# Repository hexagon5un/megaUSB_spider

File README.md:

megaUSB_spider
==============

A programming spider to make developing V-USB devices easy.

See http://littlehacks.org/propack/vusb_prototyper for more info.

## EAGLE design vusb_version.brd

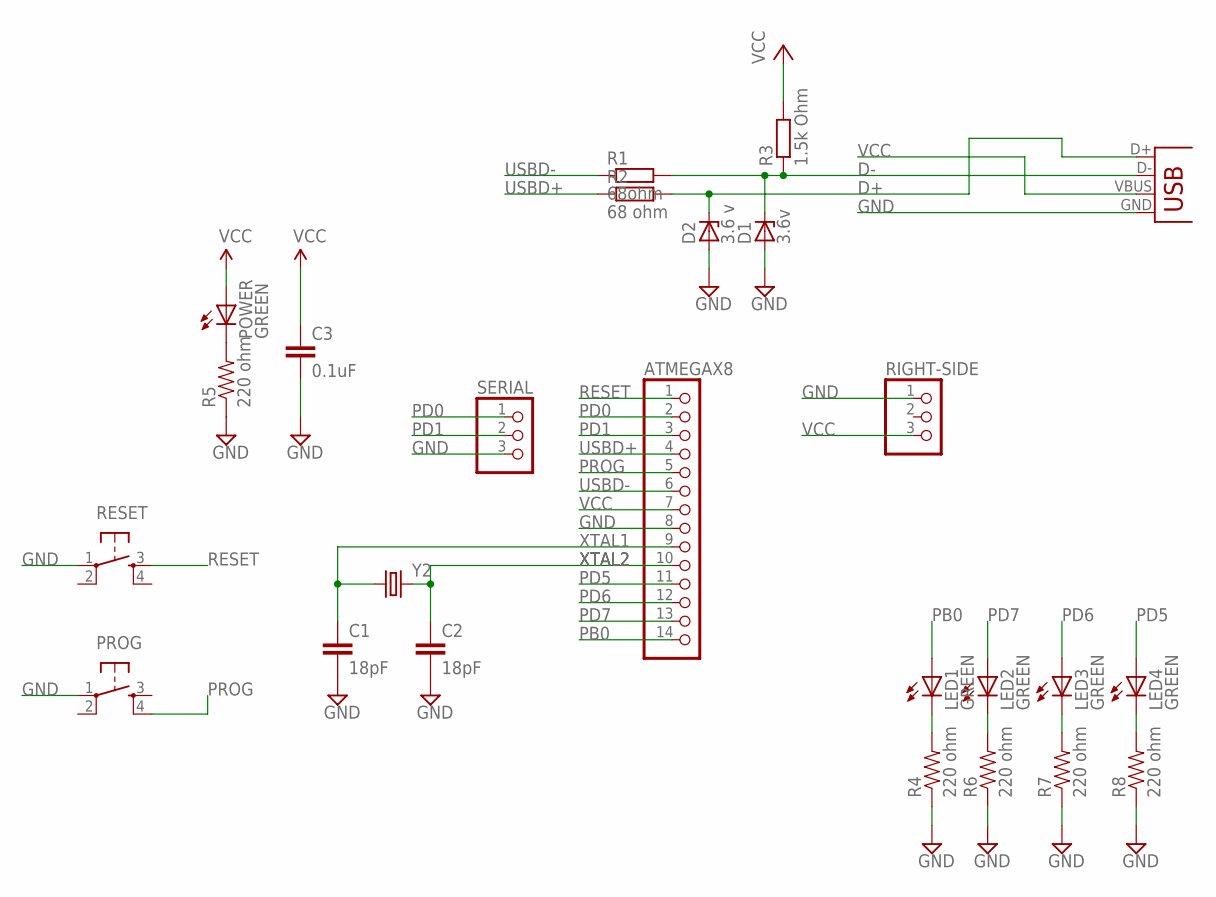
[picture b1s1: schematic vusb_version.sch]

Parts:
ATMEGAX8: PINHD-1X14; 1X14
C1, C2: 18pF; 1206
C3: 0.1uF; 1206
D1: 3.6v; SOT23
D2: 3.6 v; SOT23
JP1: USBSMD; USB-MINIB
LED1, LED2, LED3, LED4: GREEN; LED-1206
POWER: GREEN; LED-1206
PROG: TAC_SWITCHPTH; TACTILE-PTH
R1: 68ohm; R0805
R2: 68 ohm; R0805
R3: 1.5k Ohm; R1206
R4, R5, R6, R7, R8: 220 ohm; 1206
RESET: TAC_SWITCHPTH; TACTILE-PTH
RIGHT-SIDE: PINHD-1X3; 1X03
SERIAL: PINHD-1X3; 1X03
Y2: CRYSTALHC49US; HC49US

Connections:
D+: D2.3 (C), JP1.D+, R2.2
D-: D1.3 (C), JP1.D-, R1.2, R3.1
GND: ATMEGAX8.8, C1.2, C2.2, C3.2, D1.1 (A), D2.1 (A), JP1.GND, PROG.1, R4.1, R5.1, R6.1, R7.1, R8.1, RESET.1, RIGHT-SIDE.1, SERIAL.3
LED2: LED2.C, R6.2
unnamed: LED1.C, R4.2
unnamed: POWER.C, R5.2
unnamed: LED3.C, R7.2
unnamed: LED4.C, R8.2
PB0: LED1.A
PD0: ATMEGAX8.2, SERIAL.1
PD1: ATMEGAX8.3, SERIAL.2
PD5: ATMEGAX8.11, LED4.A
PD6: ATMEGAX8.12, LED3.A
PD7: ATMEGAX8.13, LED2.A
PROG: ATMEGAX8.5, PROG.4
RESET: ATMEGAX8.1, RESET.3
USBD+: ATMEGAX8.4, R2.1
USBD-: ATMEGAX8.6, R1.1
VCC: ATMEGAX8.7, C3.1, JP1.VBUS, POWER.A, R3.2, RIGHT-SIDE.3
XTAL1: ATMEGAX8.9, C1.1, Y2.1
XTAL2: ATMEGAX8.10, C2.1, Y2.2

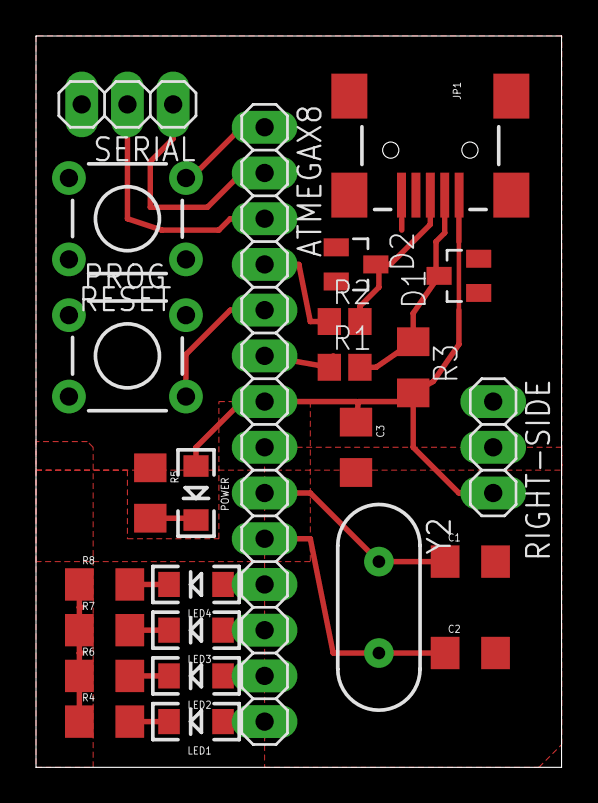
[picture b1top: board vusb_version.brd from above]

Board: 2 copper layers, 29.2 x 40.6 mm, 25 parts (0 on the bottom side), 20 nets.

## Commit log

2014-03-24 initial import, but working draft
    All wired up. Looks nice, but no space for breadboarding
    on the un-used side of the board
2014-03-24 first printed version
    works, woot.
    AVCC and opposite-side ground should be connected
    need both-sides spider, for which maybe (yet another) redesign
2014-03-24 switching pins round to match vusb demos
    (or at least some of them)
    and adding serial in/out. B/c why not.
    Also power/gnd on right side of chip.
2014-03-26 printed version 2
    debugged, optimized, working, woots.
2014-03-26 cleanup of the old versions

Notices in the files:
parts and their libraries:
SparkFun-LED: Licensing: CC v3.0 Share-Alike You are welcome to use this library for commercial purposes.
